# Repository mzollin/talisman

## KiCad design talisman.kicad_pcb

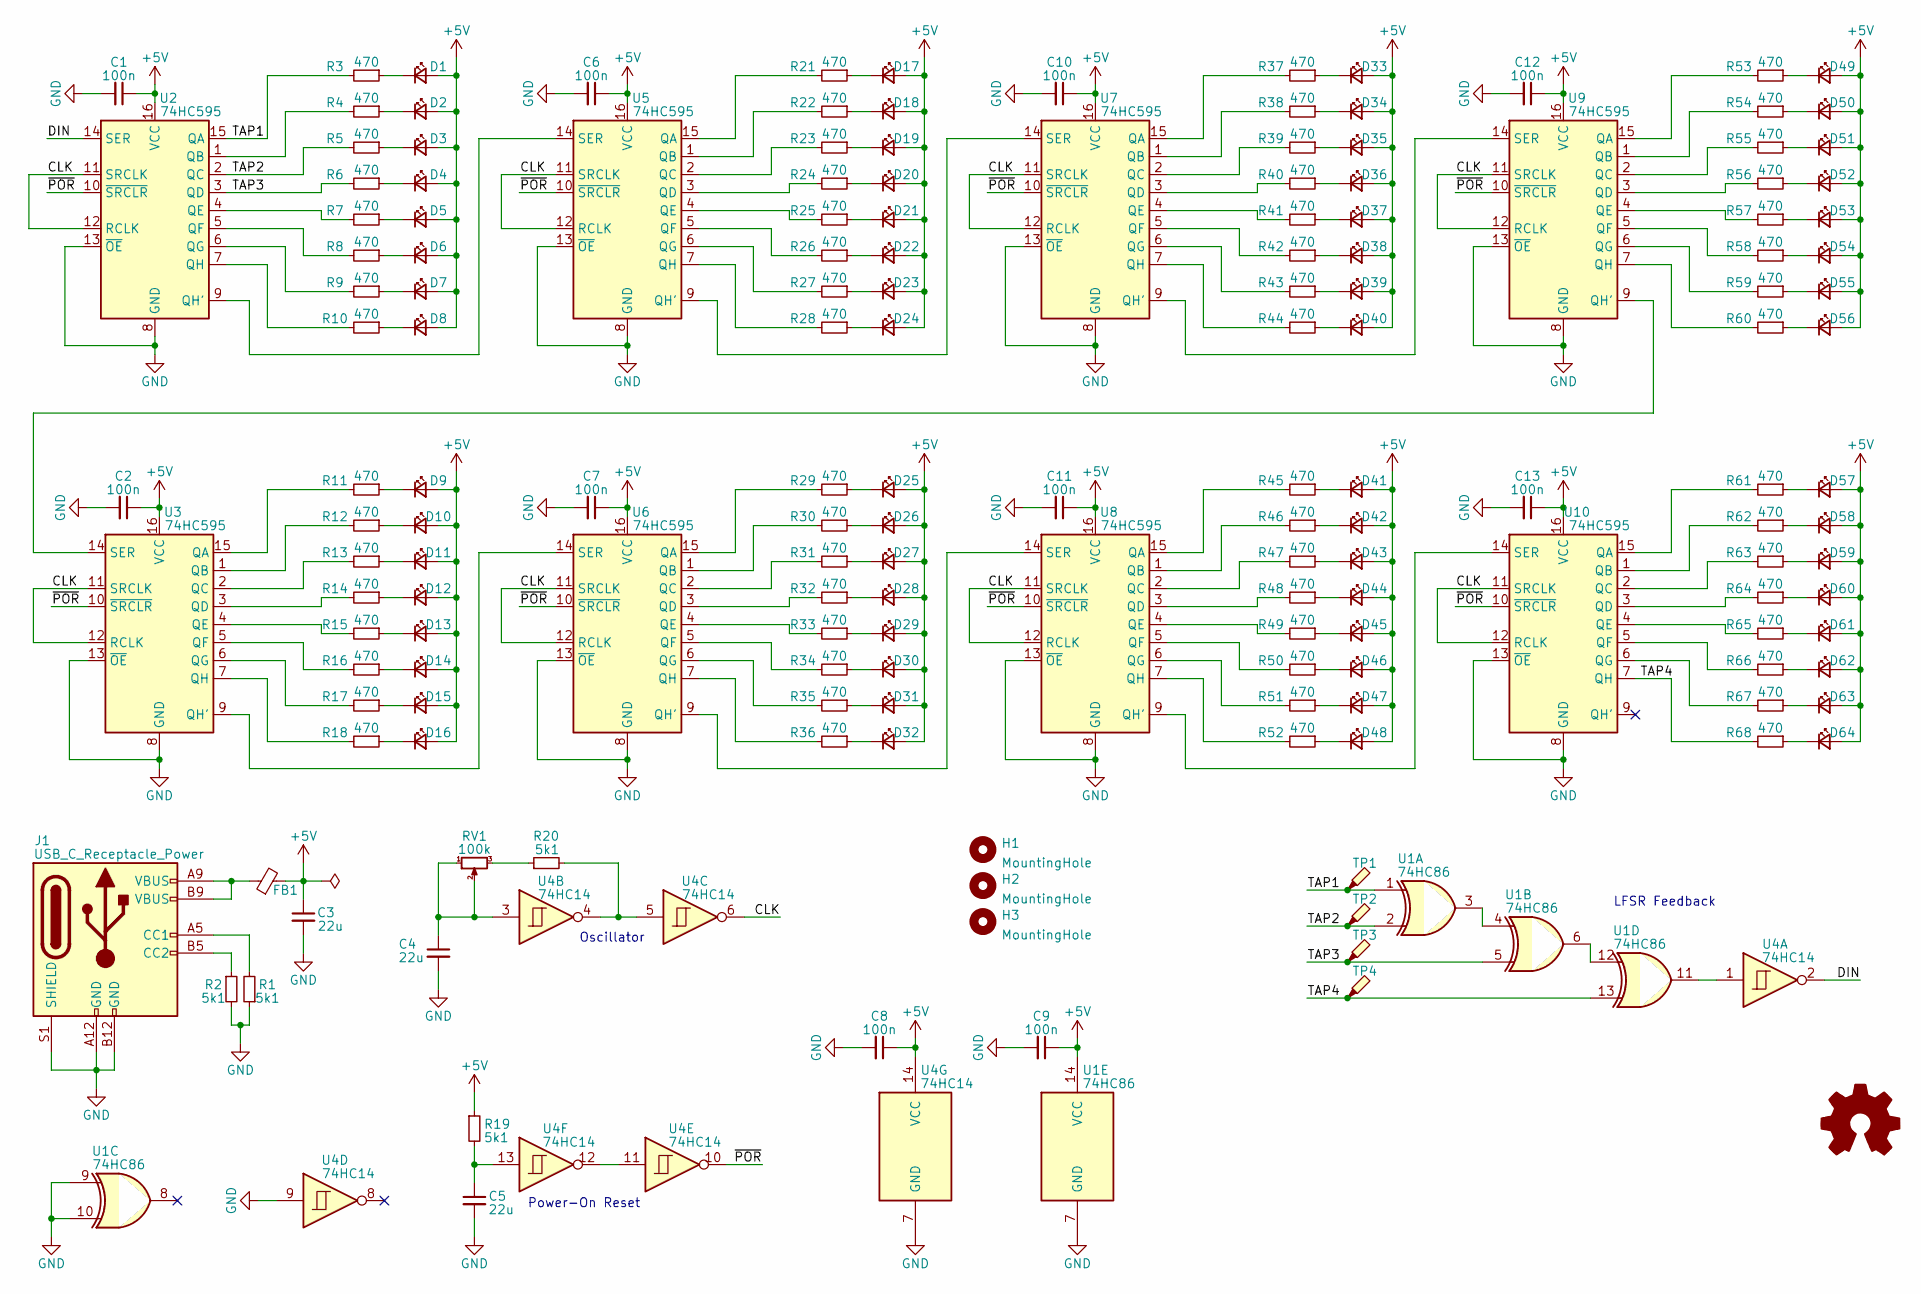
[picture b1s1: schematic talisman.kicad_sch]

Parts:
C1, C2, C6, C7, C8, C9, C10, C11, C12, C13: 100n; C_0603_1608Metric; JLCPCB Part # C14663
C3, C4, C5: 22u; C_1206_3216Metric; JLCPCB Part # C12891
D1, D2, D3, D4, D5, D6, D7, D8, D9, D10, D11, D12, D13, D14, D15, D16, D17, D18, D19, D20, D21, D22, D23, D24, D25, D26, D27, D28, D29, D30, D31, D32, D33, D34, D35, D36, D37, D38, D39, D40, D41, D42, D43, D44, D45, D46, D47, D48, D49, D50, D51, D52, D53, D54, D55, D56, D57, D58, D59, D60, D61, D62, D63, D64: LED_Small; LED_0402_1005Metric; JLCPCB Part # C264413
FB1: FerriteBead_Small; R_0805_2012Metric; JLCPCB Part # C1015
H1, H2, H3: MountingHole; MountingHole_2.7mm_M2.5
J1: USB_C_Receptacle_Power; TYPEC31M17; JLCPCB Part # C283540
R1, R2, R19, R20: 5k1; R_0603_1608Metric; JLCPCB Part # C23186
R3, R4, R5, R6, R7, R8, R9, R10, R11, R12, R13, R14, R15, R16, R17, R18, R21, R22, R23, R24, R25, R26, R27, R28, R29, R30, R31, R32, R33, R34, R35, R36, R37, R38, R39, R40, R41, R42, R43, R44, R45, R46, R47, R48, R49, R50, R51, R52, R53, R54, R55, R56, R57, R58, R59, R60, R61, R62, R63, R64, R65, R66, R67, R68: 470; R_0402_1005Metric; JLCPCB Part # C25117
RV1: 100k; G43BTB103; JLCPCB Part # C128149
TP1, TP2, TP3, TP4: TestPoint_Probe; TestPoint_Pad_D1.5mm
U1: 74HC86; SOIC-14_3.9x8.7mm_P1.27mm; JLCPCB Part # C5955
U2, U3, U5, U6, U7, U8, U9, U10: 74HC595; SOIC-16_3.9x9.9mm_P1.27mm; JLCPCB Part # C5947
U4: 74HC14; SOIC-14_3.9x8.7mm_P1.27mm; JLCPCB Part # C5605

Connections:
+5V: C1.1, C2.1, C3.1, C6.1, C7.1, C8.1, C9.1, C10.1, C11.1, C12.1, C13.1, D1.2 (A), D2.2 (A), D3.2 (A), D4.2 (A), D5.2 (A), D6.2 (A), D7.2 (A), D8.2 (A), D9.2 (A), D10.2 (A), D11.2 (A), D12.2 (A), D13.2 (A), D14.2 (A), D15.2 (A), D16.2 (A), D17.2 (A), D18.2 (A), D19.2 (A), D20.2 (A), D21.2 (A), D22.2 (A), D23.2 (A), D24.2 (A), D25.2 (A), D26.2 (A), D27.2 (A), D28.2 (A), D29.2 (A), D30.2 (A), D31.2 (A), D32.2 (A), D33.2 (A), D34.2 (A), D35.2 (A), D36.2 (A), D37.2 (A), D38.2 (A), D39.2 (A), D40.2 (A), D41.2 (A), D42.2 (A), D43.2 (A), D44.2 (A), D45.2 (A), D46.2 (A), D47.2 (A), D48.2 (A), D49.2 (A), D50.2 (A), D51.2 (A), D52.2 (A), D53.2 (A), D54.2 (A), D55.2 (A), D56.2 (A), D57.2 (A), D58.2 (A), D59.2 (A), D60.2 (A), D61.2 (A), D62.2 (A), D63.2 (A), D64.2 (A), FB1.2, R19.1, U1.14 (VCC), U2.16 (VCC), U3.16 (VCC), U4.14 (VCC), U5.16 (VCC), U6.16 (VCC), U7.16 (VCC), U8.16 (VCC), U9.16 (VCC), U10.16 (VCC)
/CLK: U2.11 (SRCLK), U2.12 (RCLK), U3.11 (SRCLK), U3.12 (RCLK), U4.6, U5.11 (SRCLK), U5.12 (RCLK), U6.11 (SRCLK), U6.12 (RCLK), U7.11 (SRCLK), U7.12 (RCLK), U8.11 (SRCLK), U8.12 (RCLK), U9.11 (SRCLK), U9.12 (RCLK), U10.11 (SRCLK), U10.12 (RCLK)
/DIN: U2.14 (SER), U4.2
/TAP1: R3.2, TP1.1, U1.1, U2.15 (QA)
/TAP2: R5.2, TP2.1, U1.2, U2.2 (QC)
/TAP3: R6.2, TP3.1, U1.5, U2.3 (QD)
/TAP4: R68.2, TP4.1, U1.13, U10.7 (QH)
/~POR: U2.10 (~SRCLR), U3.10 (~SRCLR), U4.10, U5.10 (~SRCLR), U6.10 (~SRCLR), U7.10 (~SRCLR), U8.10 (~SRCLR), U9.10 (~SRCLR), U10.10 (~SRCLR)
GND: C1.2, C2.2, C3.2, C4.2, C5.2, C6.2, C7.2, C8.2, C9.2, C10.2, C11.2, C12.2, C13.2, J1.A12 (GND), J1.B12 (GND), J1.S1 (SHIELD), R1.1, R2.2, U1.7 (GND), U1.9, U1.10, U2.8 (GND), U2.13 (~OE), U3.8 (GND), U3.13 (~OE), U4.7 (GND), U4.9, U5.8 (GND), U5.13 (~OE), U6.8 (GND), U6.13 (~OE), U7.8 (GND), U7.13 (~OE), U8.8 (GND), U8.13 (~OE), U9.8 (GND), U9.13 (~OE), U10.8 (GND), U10.13 (~OE)
unnamed: C4.1, RV1.1, RV1.2, U4.3
unnamed: C5.1, R19.2, U4.13
unnamed: D1.1 (K), R3.1
unnamed: D2.1 (K), R4.1
unnamed: D3.1 (K), R5.1
unnamed: D4.1 (K), R6.1
unnamed: D5.1 (K), R7.1
unnamed: D6.1 (K), R8.1
unnamed: D7.1 (K), R9.1
unnamed: D8.1 (K), R10.1
unnamed: D9.1 (K), R11.1
unnamed: D10.1 (K), R12.1
unnamed: D11.1 (K), R13.1
unnamed: D12.1 (K), R14.1
unnamed: D13.1 (K), R15.1
unnamed: D14.1 (K), R16.1
unnamed: D15.1 (K), R17.1
unnamed: D16.1 (K), R18.1
unnamed: D17.1 (K), R21.1
unnamed: D18.1 (K), R22.1
unnamed: D19.1 (K), R23.1
unnamed: D20.1 (K), R24.1
unnamed: D21.1 (K), R25.1
unnamed: D22.1 (K), R26.1
unnamed: D23.1 (K), R27.1
unnamed: D24.1 (K), R28.1
unnamed: D25.1 (K), R29.1
unnamed: D26.1 (K), R30.1
unnamed: D27.1 (K), R31.1
unnamed: D28.1 (K), R32.1
unnamed: D29.1 (K), R33.1
unnamed: D30.1 (K), R34.1
unnamed: D31.1 (K), R35.1
unnamed: D32.1 (K), R36.1
unnamed: D33.1 (K), R37.1
unnamed: D34.1 (K), R38.1
unnamed: D35.1 (K), R39.1
unnamed: D36.1 (K), R40.1
unnamed: D37.1 (K), R41.1
unnamed: D38.1 (K), R42.1
unnamed: D39.1 (K), R43.1
unnamed: D40.1 (K), R44.1
unnamed: D41.1 (K), R45.1
unnamed: D42.1 (K), R46.1
unnamed: D43.1 (K), R47.1
unnamed: D44.1 (K), R48.1
unnamed: D45.1 (K), R49.1
unnamed: D46.1 (K), R50.1
unnamed: D47.1 (K), R51.1
unnamed: D48.1 (K), R52.1
unnamed: D49.1 (K), R53.1
unnamed: D50.1 (K), R54.1
unnamed: D51.1 (K), R55.1
unnamed: D52.1 (K), R56.1
unnamed: D53.1 (K), R57.1
unnamed: D54.1 (K), R58.1
unnamed: D55.1 (K), R59.1
unnamed: D56.1 (K), R60.1
unnamed: D57.1 (K), R61.1
unnamed: D58.1 (K), R62.1
unnamed: D59.1 (K), R63.1
unnamed: D60.1 (K), R64.1
unnamed: D61.1 (K), R65.1
unnamed: D62.1 (K), R66.1
unnamed: D63.1 (K), R67.1
unnamed: D64.1 (K), R68.1
unnamed: FB1.1, J1.A9 (VBUS), J1.B9 (VBUS)
unnamed: J1.A5 (CC1), R1.2
unnamed: J1.B5 (CC2), R2.1
unnamed: R4.2, U2.1 (QB)
unnamed: R7.2, U2.4 (QE)
unnamed: R8.2, U2.5 (QF)
unnamed: R9.2, U2.6 (QG)
unnamed: R10.2, U2.7 (QH)
unnamed: R11.2, U3.15 (QA)
unnamed: R12.2, U3.1 (QB)
unnamed: R13.2, U3.2 (QC)
unnamed: R14.2, U3.3 (QD)
unnamed: R15.2, U3.4 (QE)
unnamed: R16.2, U3.5 (QF)
unnamed: R17.2, U3.6 (QG)
unnamed: R18.2, U3.7 (QH)
unnamed: R20.1, RV1.3
unnamed: R20.2, U4.4, U4.5
unnamed: R21.2, U5.15 (QA)
unnamed: R22.2, U5.1 (QB)
unnamed: R23.2, U5.2 (QC)
unnamed: R24.2, U5.3 (QD)
unnamed: R25.2, U5.4 (QE)
unnamed: R26.2, U5.5 (QF)
unnamed: R27.2, U5.6 (QG)
unnamed: R28.2, U5.7 (QH)
unnamed: R29.2, U6.15 (QA)
unnamed: R30.2, U6.1 (QB)
unnamed: R31.2, U6.2 (QC)
unnamed: R32.2, U6.3 (QD)
unnamed: R33.2, U6.4 (QE)
unnamed: R34.2, U6.5 (QF)
unnamed: R35.2, U6.6 (QG)
unnamed: R36.2, U6.7 (QH)
unnamed: R37.2, U7.15 (QA)
unnamed: R38.2, U7.1 (QB)
unnamed: R39.2, U7.2 (QC)
unnamed: R40.2, U7.3 (QD)
unnamed: R41.2, U7.4 (QE)
unnamed: R42.2, U7.5 (QF)
unnamed: R43.2, U7.6 (QG)
unnamed: R44.2, U7.7 (QH)
unnamed: R45.2, U8.15 (QA)
unnamed: R46.2, U8.1 (QB)
unnamed: R47.2, U8.2 (QC)
unnamed: R48.2, U8.3 (QD)
unnamed: R49.2, U8.4 (QE)
unnamed: R50.2, U8.5 (QF)
unnamed: R51.2, U8.6 (QG)
unnamed: R52.2, U8.7 (QH)
unnamed: R53.2, U9.15 (QA)
unnamed: R54.2, U9.1 (QB)
unnamed: R55.2, U9.2 (QC)
unnamed: R56.2, U9.3 (QD)
unnamed: R57.2, U9.4 (QE)
unnamed: R58.2, U9.5 (QF)
unnamed: R59.2, U9.6 (QG)
unnamed: R60.2, U9.7 (QH)
unnamed: R61.2, U10.15 (QA)
unnamed: R62.2, U10.1 (QB)
unnamed: R63.2, U10.2 (QC)
unnamed: R64.2, U10.3 (QD)
unnamed: R65.2, U10.4 (QE)
unnamed: R66.2, U10.5 (QF)
unnamed: R67.2, U10.6 (QG)
unnamed: U1.3, U1.4
unnamed: U1.11, U4.1
unnamed: U1.6, U1.12
unnamed: U2.9 (QH'), U5.14 (SER)
unnamed: U3.9 (QH'), U6.14 (SER)
unnamed: U3.14 (SER), U9.9 (QH')
unnamed: U4.11, U4.12
unnamed: U5.9 (QH'), U7.14 (SER)
unnamed: U6.9 (QH'), U8.14 (SER)
unnamed: U7.9 (QH'), U9.14 (SER)
unnamed: U8.9 (QH'), U10.14 (SER)

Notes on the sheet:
Oscillator
Power-On Reset
LFSR Feedback

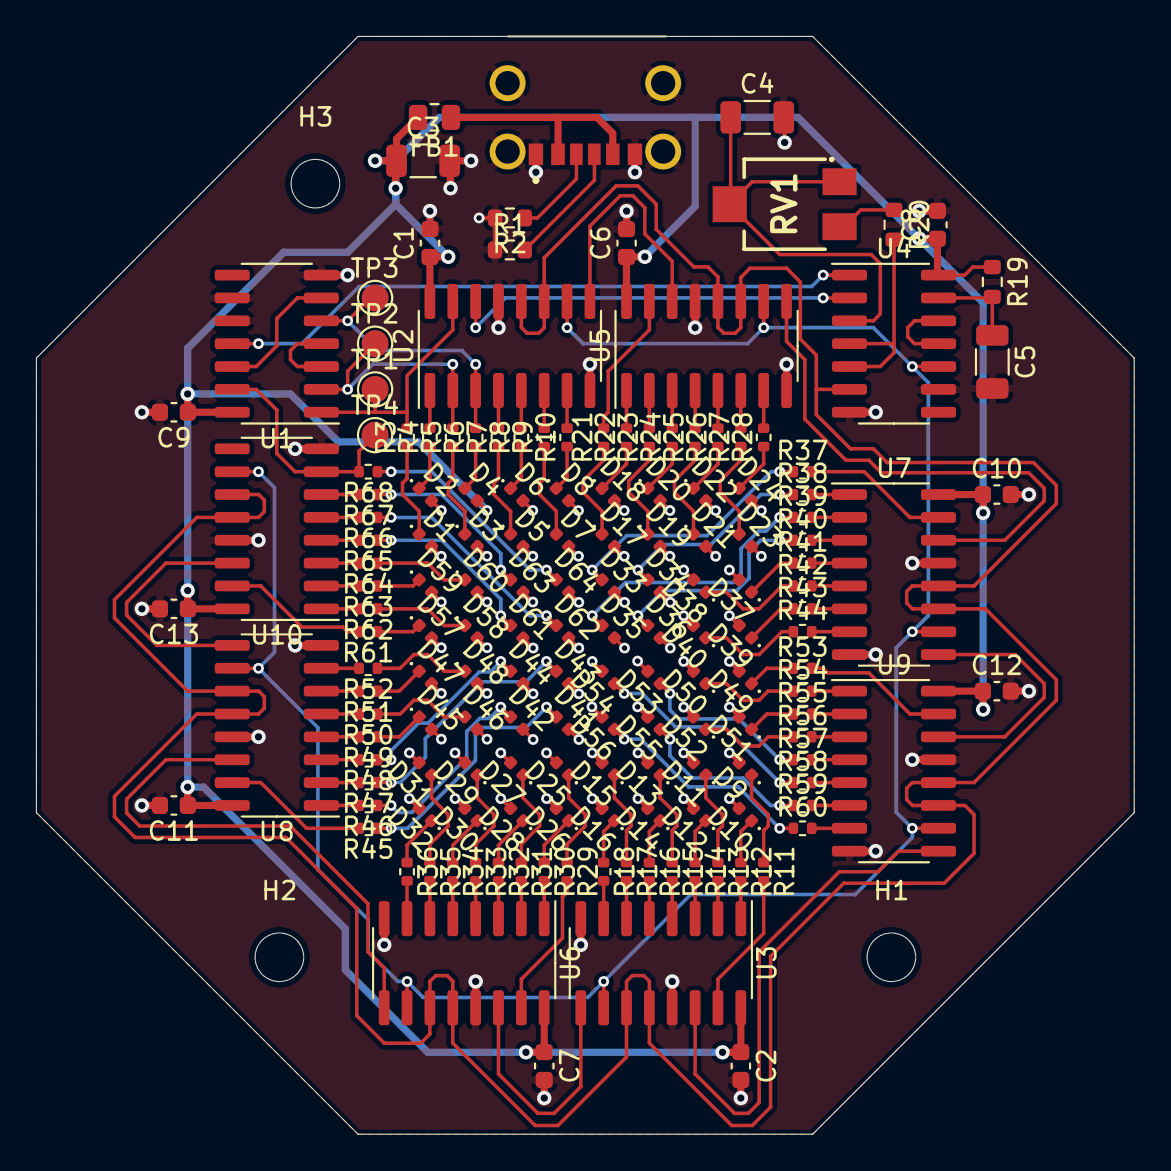
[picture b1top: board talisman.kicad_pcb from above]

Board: 2 copper layers, 61.0 x 61.0 mm, 166 parts (0 on the bottom side), 151 nets.

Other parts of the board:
QR*****: github.com/mzollin/talisman; github.com_mzollin_talisman

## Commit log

2022-02-11 Adapt MIT license to Open Source Hardware
2022-02-11 Add design source files
2022-02-11 Add 3D rendering pictures front and rear
